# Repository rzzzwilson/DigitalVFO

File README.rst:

Digital VFO
===========
 
About
=====

I'm an amateur radio operator, but since I'm not in the country in which I
earned my licence I can't actually build or operate a transmitter, so I build
receivers and test gear.  I'm working on being able to operate from my
country of residence, but that's another story.

One piece of test gear that would be useful is called a Signal Generator.  This
is a piece of kit that generates a radio signal of a known frequency.  It can
also be used as a VFO (variable frequency oscillator) in a receiver.

The modern way to accurately generate an RF signal is to use the AD9851 DDS chip
which digitally generates a known frequency from a crystal source.  There are 
quite a few people offering small boards using this chip but I like the
`DDS-60 daughterboard <http://midnightdesignsolutions.com/dds60/>`_
from `Midnight Design Solutions <http://midnightdesignsolutions.com/>`_.
All I need to do is use a microcontroller to control the DDS-60 with some
sort of frequency display!

The obvious solution is to use an Arduino and the ubiquitous 16x2 display.
Since the Arduino is a little large and I hoped to put the kit into a small
case I decided to use a
`Teensy microcontroller <https://www.pjrc.com/store/teensy32.html>`_
which is programmable through the Arduino IDE.  It's about 35mm x 18mm!
It's a very capable little microcontroller and is overkill for this project,
but it's what I have at the moment.  I'm working on a
`smaller "generic" design <https://github.com/rzzzwilson/KiCad_Projects/tree/master/Iota>`_
that I can fit into any PCB projects that need smarts.

I got a couple of generic 16x2 displays from
`AliExpress <https://www.aliexpress.com/wholesale?catId=0&initiative_id=SB_20170504210259&SearchText=display+1602>`_.
I got the rotary encoder from
`the same place <https://www.aliexpress.com/wholesale?catId=0&initiative_id=AS_20170504210300&SearchText=rotary+encoder+switch>`_.

Schematic
=========

The latest code runs on this hardware arrangement:

.. image:: DigitalVFO_1.4_Schematic.png

PCB
=========

The 1.4 PCB looks like this:

.. image:: DigitalVFO_1.4_PCB.png

Status
======

.. image:: DigitalVFO_case.jpg

Version 1.4 is running as shown above!  There is provision for a battery plus
monitoring of the voltage and calibration of various things.  There will be another
version called "HeadlessVFO" that will be controlled only by a PC via USB.  This
version won't need a display or rotary encoder, plus it'll always be
connected to a PC and get USB power, so no battery.  I probably don't need
a Teensy 3.2 to drive HeadlessVFO, so I'm searching for cheap microcontrollers
on AliExpress that can accept text commands from the USB connection.

13 Sept: Looking at the AtMega32U4.  A similar chip is used in the Arduino UNO
R3 instead of the FTDI FT232RL USB interface chip, but the AtMega is quite
capable and can control the HeadlessVFO so I won't need any special USB
interface chip.  Anyway, that's the current plan.

Version 1.5
===========

5 May 2019 Update
-----------------

Noted corruption of the display and things like saved frequencies.  The DDS-60
was being set to a **negative** frequency!  Investigated, but suspect this
problem was caused by interference by connecting USB power to the Teensy while
the VFO was running from the battery.  Debug by connecting USB power AT THE PC
while the VFO is off.  See if the problem reoccurs whie doing that.

Early 2019
----------

Modified the PCB layout to include test points for battery voltage, RF out, ground, etc.

Version 1.4
===========

13 September Update
-------------------

The battery arrived but it won't fit into the case.  Instead I'm using the two
18650 test cells with a small BMS PCB, all wrapped in a piece of heat-shrinkable
tubing.  I've bypassed the polarity protection diode as it eats a volt from the
battery.  Working well, but I've found that the power switch I used is a little
unreliable.  That needs to be replaced - the replacement is on a slow boat from
China.

03 July Update
--------------

Still waiting for a 7.4v battery from China.  When it arrives I'll experiment
with the monitoring software.  I may remove the 'polarity' diode once I have
cables made up.  It removes about a volt from the battery and the DDS-60 was
cutting out long before the battery was empty.

21 June Update
--------------

The case is finished.  When/if a permanent battery is installed I'll drill
a few holes for a switch and a 9v charging port.  The software for commands
from the PC is basically finished.  I removed a lot of stuff not necessary
for using the DigitalVFO in an instrument cluster.

19 May Update
-------------

The 1.4 board is back from Seeed, built and operating.  This version has
provision for the micro to sense the battery voltage so it can display
a battery symbol with full/empty options.
Software development time!

Version 1.3
===========

A redesign to use another BNC connecter as the first was junk.
Not sent to Seeed as I also decided to add battery monitoring.

Version 1.2
===========

After building the v1.1 PCB and paddling around on aliexpress.com to find
different components, I'm starting on the v1.2 PCB.  Should be smaller, have
the LCD located in a more natural place and place controls in more natural 
positions.  May also rethink the power supply - perhaps run both board and
DDS-60 from a 78L05 instead of running 9v to DDS-60 and using the onboard
regulator to generate 5v for the main board.  Use the same case as before.

29 March Update
---------------

Version 1.2 of the PCB submitted to Seeed today.  Changes were:

* moved components around to minimize vias
* on-board BNC socket, saves on internal cables
* moves Teensy to edge so USB goes through case, saves on internal cables
* added provision for internal 2s Li-Ion battery and manager PCB feeding the DDS-60
* added provision for LED power in battery power switch

Version 1.1
===========

Need to:

* new case allows in-case programming
* new case has ventilation (passive at first)
* better packaging (printed circuit board)
* better, more linear, contrast control

And, of course:

* allow control over USB
* maybe add a "sweep" function to the in-case code (from, to, step, pause)
* look for bugs in the software

With PC control we can measure things with a "sweep" function.  Allow the PC to
control the VFO frequency and the PC can sweep the frequency to whatever limits
required.  At the same time, measure voltage/current/whatever from other Teensy
instruments.  This means we could build:

* an antenna analyzer
* measure filter response curves
* etc

This version will use a printed circuit board to address the general
unreliability of the 1.0 version.  The LCD will plug into the back of the main
PCB and the DDS-60 will plug into the front.  The rotary encoder will have a
cable with header that will plug into the PCB.

The file **DigitalVFO_Schematic_1.1.pdf** is the schematic of the circuit.  The
directory **kicad/DigitalVFO/Gerbers** holds the output files produced by KiCad.
The Gerber files were sent to a Chinese PCB fab factory.

The PCB has now returned from China, and it does look good.  Better yet,
assembling the board and testing it shows the thing WORKS!  I had to change the
code to match changes I made while setting out the PCB, BUT IT WORKS!!

Version 1.0
===========

The VFO hardware is complete.  Everything is inside a small metal case.  Perhaps
too small a metal case as running at 12v the thing overheats and becomes
unreliable.  It seems OK at 9v.  I also didn't think about accessing the Teensy
USB port when the case is closed, so I can't tweak the software without cracking
the case, which I can't do often as the wiring inside is fragile.

Completed:

* Interface display to teensy, test writing, etc
* Interface rotary encoder, get rotate and button press events
* Basic display of 8-digit frequency
* Implement a simple 'event' system to produce system events
* Get frequency column select and increment/decrement working
* Save state in the EEPROM, restore state on start up
* implement a simple menu system 
* extend the menu system to allow extra functionality
* added vfo_DClick double-click event
* add code to toggle standby/ON mode (from vfo_DClick)
* add in the DDS-60 control code
* add a "Calibrate" setting to adjust the divider value in the DDS-60 code
* test the thing fully!
* make up a metal case and rebuild into it

Perhaps:

* make another case with USB access
* think about making a circuit board for it (Fritzing, cheap Chinese PCB maker?)

Ongoing:

* look for bugs in the software
* maybe add a "sweep" function to the code (from, to, step, pause)
* split out the Arduino code samples showing RE handling and menu system
* think about hardware assembly methods to make DigitalVFO version 2!

Interface
=========

I don't need a lot of functionality in this VFO, I just want to:

* set a frequency from 1.000000Mz to 30.000000MHz with steps down to 1Hz
* save and restore a number of frequencies

It should be possible to do all this with an interface made up of:

* A 16x2 display, and
* A rotary encoder, with switch.

Using the above the user can move a 'column selection' indication in the
frequency display by pressing down on the encoder knob and then rotating it.
With the knob up, rotation just increments or decrements the
selected digit with over- and under-flow occurring to the left of the
selected digit.  This is pretty much the way everybody does it.

It would also be nice if the VFO remembered the frequency and selected digit if
the power is lost and then restored.  Use the on-board EEPROM for this, as well
as remembered frequencies.

We may have to come up with some way of having a simple menu-driven method
of:

* Saving/restoring frequencies
* Adjusting various internal parameters such as clock scaling, etc.

We could possibly drop into the menu system if the encoder knob is held down
for some length of time.

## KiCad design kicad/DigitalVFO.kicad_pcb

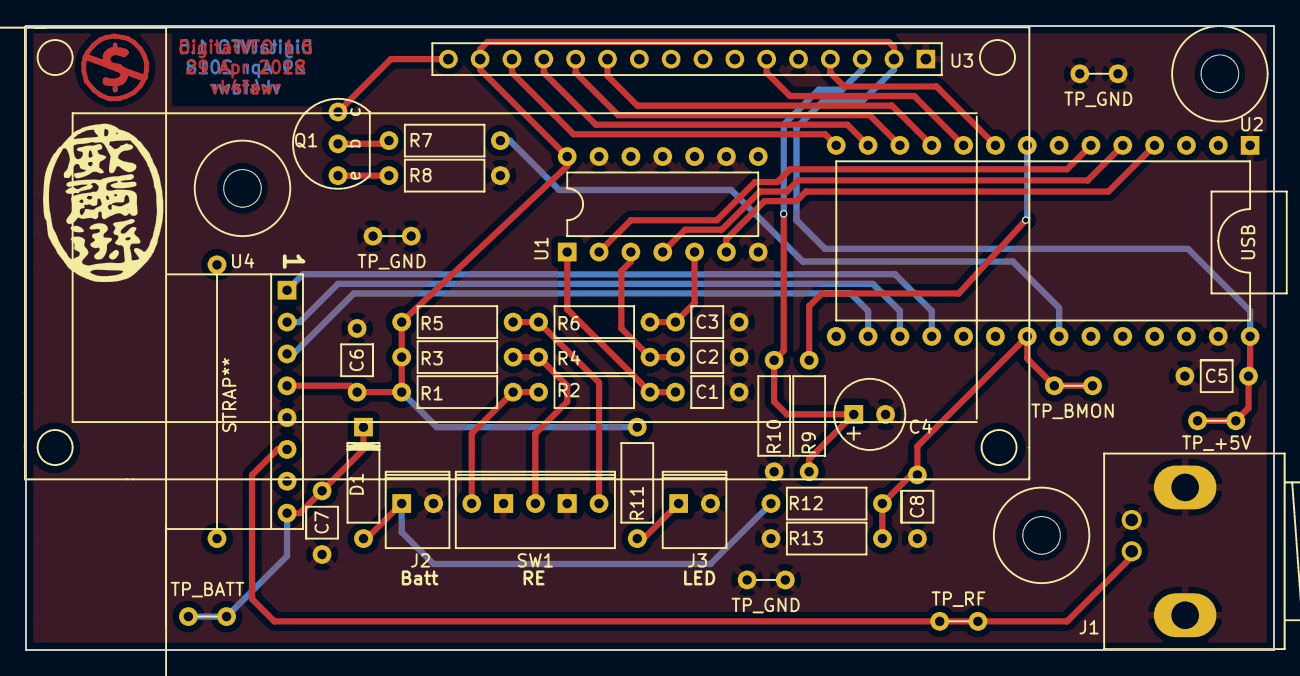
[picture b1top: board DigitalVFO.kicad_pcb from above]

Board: 2 copper layers, 99.6 x 49.8 mm, 39 parts (0 on the bottom side), 31 nets.

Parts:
C1, C2, C3, C5, C6, C7, C8: 0.1uF; Cap_SmV
C4: 100uF; Conn_CElec_v
D1: 1N4001; Diode_SmH
J1: RF Out; BNC_Socket_TYCO-AMP
J2: Battery; Conn_Power_2
J3: SW_LED; Conn_Power_2
Q1: 2N2222A; Con_2N222A
R1, R3, R5: 100K; Res_SmH
R2, R4, R6, R13: 10K; Res_SmH
R7: 15K; Res_SmH
R8: 10R; Res_SmH
R9, R10: 1K; Res_SmH
R11: 0R0; Res_SmH
R12: 22K; Res_SmH
STRAP**: Strap_22
SW1: Rotary_Encoder; Conn_RE_Switch
TP_+5V: TestPoint
TP_BATT: TestPoint
TP_BMON: TestPoint
TP_GND: TestPoint
TP_GND#2, TP_GND#3: TestPoint
TP_RF: TestPoint
U1: 74HC14; Conn_DIP14n
U2: Teensy3.2; Conn_DIP28w
U3: LCD1602A; Conn_LCD16
U4: DDS-60; Conn_DDS8

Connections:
+5V: C5.1, C6.1, R1.1, R3.1, R5.1, R11.1, TP_+5V.1, TP_+5V.2, U1.14, U2.28, U3.2, U3.15, U4.4
/BATT: C7.1, D1.1, TP_BATT.1, TP_BATT.2, U4.8
/BMON: C8.1, R12.2, R13.1, TP_BMON.1, TP_BMON.2, U2.21
/RF: J1.1, TP_RF.1, TP_RF.2, U4.6
GND: C1.2, C2.2, C3.2, C4.2, C5.2, C6.2, C7.2, C8.2, J1.2, J2.2, J3.2, R8.2, R10.2, R13.2, SW1.2, SW1.4, TP_GND.1, TP_GND.2, TP_GND#2.1, TP_GND#2.2, TP_GND#3.1, TP_GND#3.2, U1.7, U1.9, U1.11, U1.13, U2.1, U2.27, U3.1, U3.5, U4.5
unnamed: C1.1, R2.2, U1.1
unnamed: C2.1, R4.2, U1.3
unnamed: C3.1, R6.2, U1.5
unnamed: C4.1, R9.1, R10.1, U3.3
unnamed: D1.2, J2.1, R12.1
unnamed: J3.1, R11.2
unnamed: Q1.1, R8.1
unnamed: Q1.2, R7.1
unnamed: Q1.3, U3.16
unnamed: R1.2, R2.1, SW1.5
unnamed: R3.2, R4.1, SW1.3
unnamed: R5.2, R6.1, SW1.1
unnamed: R7.2, U2.22
unnamed: R9.2, U2.8
unnamed: U1.2, U2.6
unnamed: U1.4, U2.5
unnamed: U1.6, U2.4
unnamed: U2.9, U3.4
unnamed: U2.10, U3.6
unnamed: U2.11, U3.11
unnamed: U2.12, U3.12
unnamed: U2.13, U3.13
unnamed: U2.14, U3.14
unnamed: U2.16, U4.3
unnamed: U2.17, U4.2
unnamed: U2.18, U4.1

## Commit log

2017-05-05 Added README
2017-05-05 Renamed code to final name
2017-05-05 Fiddling with RST formatting
2017-05-05 Fix spelling errors
2017-05-05 Expanding
2017-05-05 Add FIXME about only using *one* CGRAM character
2017-05-05 Initial commit of design document
2017-05-05 Adding to design document
2017-05-05 Implemented proper event handling
2017-05-06 Start implementing menus
2017-05-06 Basic menu code working
2017-05-06 Expanding menu code
2017-05-06 Expand README comments
2017-05-06 Expanding design notes
2017-05-06 Removed interrupt disable
2017-05-07 Added name/version, debug code
2017-05-07 Added a dynamic banner
2017-05-07 Still fiddling with menu code
2017-05-07 Still cleaning up menu handling
2017-05-08 Menus mostly working
2017-05-08 Menus working, bumped version number
2017-05-08 Updated status
2017-05-09 Sometimes get random events on startup, flush them
2017-05-09 Indicate that slot freq is the current freq. Close #2
2017-05-09 Added 'flash' to all actions
2017-05-09 Removed a lot of debug, general clean up
2017-05-09 Fixed bug when decreasing freq
2017-05-10 Bumped version to 0.7 for s/w contrast/brightness control
2017-05-10 Contrast control working
2017-05-10 Expanding the design doc
2017-05-11 Brightness and contrast now software controlled
2017-05-12 Start adding code for DDS-60
2017-05-14 Rewriting menus, zeroing incdec handler address??
2017-05-14 Rewriting menus, test brightness works
2017-05-15 'Prod' menus: bright/contrast working
2017-05-15 Working on save/restore/delete slot menus
2017-05-16 Menus now working
2017-05-16 Update status
2017-05-17 Clean up, implemented HoldClick time in Settings
2017-05-18 Now using Serial.printf()
2017-05-18 Better reset option during startup, close #6
2017-05-18 Added 'reset' menu option - close #7
2017-05-18 Removed old code, etc
2017-05-19 Some minor tweaks
2017-05-19 Implemented double-click in RE code
2017-05-19 Added to design doc
2017-05-19 Using DClick to toggle VFO mode
2017-05-20 Small change to 'online' display text
2017-05-20 Clean up and implemented 'calibrate' submenu
2017-05-20 General cleanup and simplification
2017-05-21 Rearranged a lot of code, better interrupt handling
2017-05-21 Imprived the contrast settings handling
2017-05-21 Better 'in use' char display
2017-05-21 Fixed spelling error
2017-05-24 Fixed issue #15
2017-05-24 Fixed issue #14
2017-05-24 Fixed issue #16 - Slots submenu
2017-05-24 Updated design doc
2017-05-26 Minor cleanup and code revies
2017-05-28 Spelling error, forcing B/C to debug display
2017-05-30 Documented the menu system
2017-06-09 Added MP4 and the usual Apple junk files
2017-06-09 Removed debug prints
2017-06-09 Doc on calibration
2017-06-15 Added schematic PNG
2017-06-15 Included schematic
2017-06-15 Fixed labelling error
2017-06-15 Sigh. Added missing wire
2017-11-14 Slight format fixup
2017-11-14 Add v1.1 to the doc
2017-11-19 Changes?
2017-11-20 Added contrast voltage smoothing in circuit
2017-11-26 Contrast works with USB or 9v power
2017-12-05 Documented the SCH/PCB files
2017-12-05 Added PCB/SCH files
2017-12-05 Clean up the text
2018-01-05 changed ignored files
2018-01-05 Initial commit -f KiCad files
2018-01-05 Added *production* schematic
2018-01-05 Added KiCad notes and production files
2018-01-05 Minor changes
2018-01-10 Rename doc files to show version
2018-01-10 Code changed to match 1.1 schematic
2018-01-10 Added PNG for new schematic
2018-01-11 Bumped minor revision by 1
2018-01-13 Fixed confusion around RE socket
2018-01-13 Close #17
2018-01-13 Restore only good freq from slot - close #21
2018-01-13 Only save freq to EEPROM when DDS goes online
2018-01-14 Basic external command mechanism started
2018-01-14 Finished initial command set
2018-01-14 Added 'ID;' command to identify device
2018-01-28 Spelling error
2018-02-12 Changing footprints and smaller board
2018-02-12 Start of DigitalVFO USB control code
2018-02-15 Document v1.2
2018-02-23 Better contrast control, H;, BR; & BS; commands
2018-02-23 Working on new PCB
2018-02-23 Restart working, reboot isn't
2018-02-23 New footprint
2018-03-18 New footprints
2018-03-18 Almost ready with v1.2
2018-03-23 Ignore KiCAD *bak files
2018-03-23 Final version?
2018-03-29 Removed old project
2018-03-29 V1.2 schematic
2018-03-29 New KiCad project
2018-03-29 Updated README for 1.2
2018-04-27 Version 1.4
2018-04-29 v1.5 - more compact layout
2018-05-19 Ignore everything in the 'gerber' directory
2018-05-19 Add a lot more debug
2018-05-20 Additional footprints
2018-05-20 Added testpoints and 1602A mount holes
2018-05-20 Minor fix to display - don't show old text on reload
2018-05-20 Moved track away from LCD mount hole
2018-05-20 Added voltage measurement and battery indicator
2018-05-20 Made battery stuff optional compile
2018-05-21 Fixed bug setting brightness
2018-05-21 Cleanup and better battery reporting
2018-05-23 Experimental program to control VFO
2018-05-23 Endless control
2018-06-04 Remove some external commands and cleanup
2018-06-04 'ID;' command returns program name and version
2018-06-04 Ignore editor swap files
2018-06-04 Better device checking
2018-06-21 Updated status more fully
2018-06-21 Fixed a spelling error
2018-06-23 Added newer schematic/PCB pictures
2018-07-01 Faffing around trying to recognize serial port from USB device.
2018-07-01 Meaningless meanderings
2018-07-03 Bumped 'build' number by one, ready for battery changes
2018-07-03 Status update
2018-07-09 Sort of calibrated the battery
2018-07-09 Better contrast control
2018-07-11 Calibrated the battery monitoring, a bit
2018-07-14 Filtering on Teensy
2018-07-14 Show all devices
2018-07-14 Plot charge/discharge curves
2018-07-15 Calibrated a little more, better battery symbol
2018-07-15 Better battery test monitoring software
2018-07-15 Modified to use isoformat dates
2018-07-16 Collect voltage data
2018-07-16 Better track layout
2018-07-16 Turn off debug reporting
2018-07-18 Fixed BUG in battery reporting code
2018-07-18 Forced all strings into PROGMEM
2018-07-18 Removed unused char buffer (2048 bytes)
2018-07-18 Cleaned up voltage measuring code
2018-07-18 General cleanup
2018-07-18 Added back silkscreen for test points
2018-07-18 OSHW symbol added, not used yet
2018-07-18 Removed routines replaced by stdlib code
2018-08-31 Modify code to recognize the FTDI interface
2018-08-31 Test Serial I/O on the AtMega329P-AU breadboard
2018-09-08 Fixed output format
2018-09-10 Ignore image files and SAVE files
2018-09-10 Save this, might be important
2018-09-10 Fixed problem with second immediate run not working
2018-09-10 Cleaned up for publication
2018-09-11 Added the Arduino sketch to test serial comms
2018-09-11 Cleaned up serial test code more
2018-09-13 Updated the status
2018-09-16 Improved error handling
2018-10-12 Updated callsign, voltage now averaged
2018-10-13 New scharge data
2018-10-13 Test of SSH change
2018-10-13 Better layout of the README
2018-11-23 Updated the PCB
2019-02-22 Setting a more accurate percent battery figure
2019-02-22 Thinking about putting ',' in frequency display
2019-02-24 Putting in Voltage Calibrate
2019-02-24 KiCad update?
2019-02-25 Debugging freq calibrate save problem
2019-02-25 Debugging volts calibrate save problem
2019-02-27 Added voltage calibration
2019-02-28 Volts calibrate done, plus cleanup.
2019-03-02 Checking plus cleanup
2019-03-02 Added pic of finished device
2019-03-03 Testing the clone circuit
2019-03-03 Just fiddling
2019-03-11 Add iota link
2019-03-12 Fixed problem not updating DDS-60 frequency
2019-04-08 Small changes
2019-05-05 Investigating odd behaviour
2019-05-05 Update on the corrution problem
2019-05-05 Generated images of 1.5 schematic
2019-06-20 Start 1.6 version - cleanup
2019-07-06 Tried different 'cursor' presentation, failed
2019-09-30 Added scale/range code
2020-04-03 Slightly better checking for overwriting the EEPROM
2020-04-06 v1.6.1 - better screen and Serial handling
2020-04-06 1.6.2 - close #32 - corruption
2020-04-07 1.6.3 - rationalized frequency handling
2020-04-21 Modified frequency display to use commas
2020-09-17 Just fiddling, checking battery voltage
2021-06-14 Minor version to '.2' for next release
